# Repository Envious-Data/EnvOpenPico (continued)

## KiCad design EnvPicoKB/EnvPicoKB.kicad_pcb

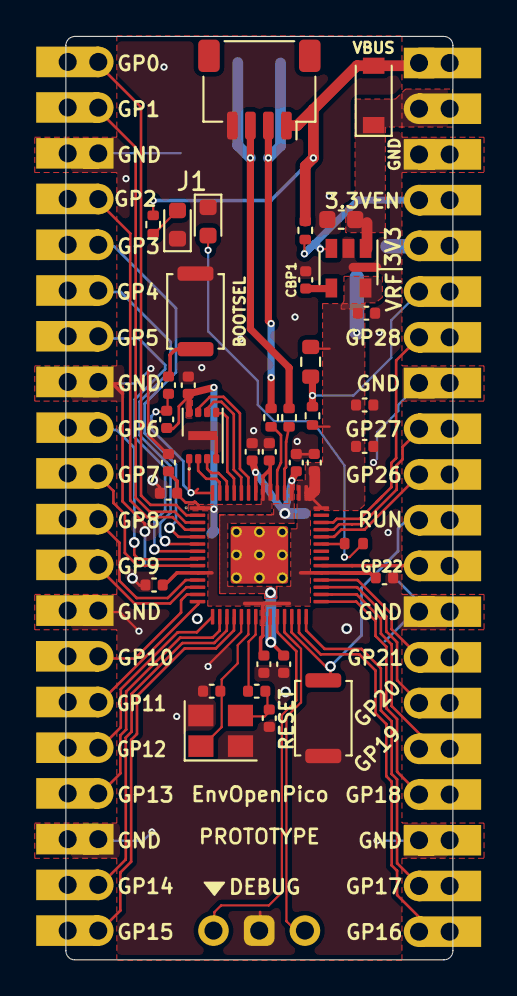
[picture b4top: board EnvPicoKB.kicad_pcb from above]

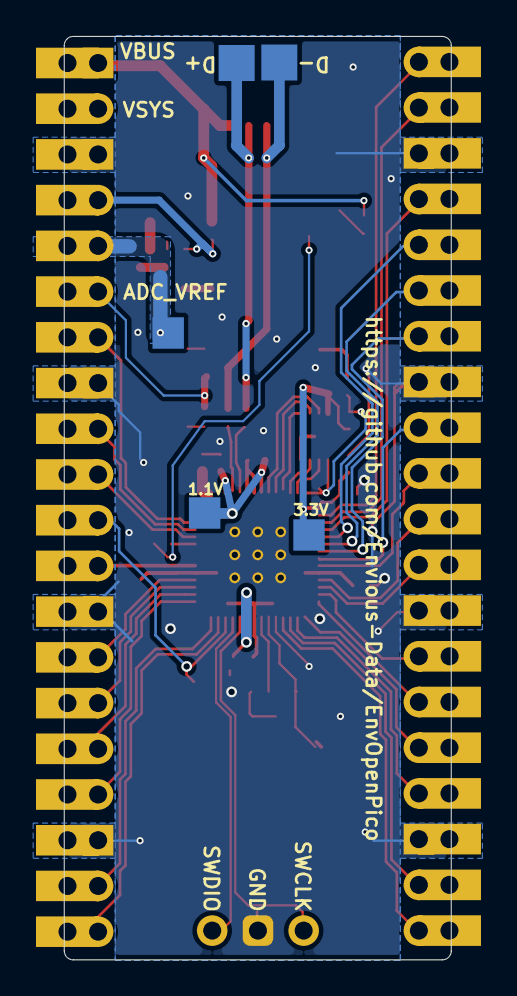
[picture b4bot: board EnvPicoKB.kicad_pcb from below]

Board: 2 copper layers, 21.5 x 51.3 mm, 46 parts (7 on the bottom side), 54 nets.

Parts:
C1: 10uf 0603 6.3V; C_0603_1608Metric
C2, C19: 22pf 0402; C_0402_1005Metric
C3, C10: 1uf 0402; C_0402_1005Metric
C4, C17: 10uf 0402; C_0402_1005Metric
C5, C6, C7, C8, C11, C13, C14, C15, C16, C18: 100nf 0402; C_0402_1005Metric
CBP1: 10uf 0402; C_0402_1005Metric
D1: 1N4002W; D_SOD-123
D3: LED_0603; LED_0603_1608Metric
FLASH1: W25Q16FWUXIE; SON-8-1EP_3x2mm_P0.5mm_EP1.4x1.6mm
J1: Conn_01x04; JST_SH_SM04B-SRSS-TB_1x04-1MP_P1.00mm_Horizontal
J2: SKRKAEE020; SW_Push_SPST_NO_Alps_SKRK
J3, J4: 2.54mm header 01x20; PinHeader_1x20_P2.54mm_Vertical
J5: Conn_01x03_Male; PinHeader_1x03_P2.54mm_Vertical
PWRLED1: LED_0603; LED_0603_1608Metric
R1, R11: 1K 0402 Resistor; C_0402_1005Metric
R2: 10K 0402; C_0402_1005Metric
R3, R4: 27 0402 Resistor; R_0402_1005Metric
R7: 100K 0402 resistor; R_0402_1005Metric
R8: 470 0402 Resistor; R_0402_1005Metric
R9: 200 0603; R_0603_1608Metric
R10: 1 0402; R_0402_1005Metric
R12: 5.1K 0402 Resistor; R_0402_1005Metric
RSW1: SKRKAEE020; SW_Push_SPST_NO_Alps_SKRK
TP1, TP2, TP6, TP7, TP8: TestPoint; TestPoint_Pad_D1.0mm
U1: TLV75533PDBVR; SOT-23-5
U3: RP2040; RP2040-QFN-56
Y1: 3225_4P; Crystal_SMD_3225-4Pin_3.2x2.5mm

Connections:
3V3_EN: J4.4, R7.1, U1.3
+1V1: C3.1, C6.1, C7.1, TP7.1, U3.23, U3.45, U3.50
+3V3: C4.1, C5.1, C8.1, C10.1, C11.1, C13.1, C14.1, C15.1, C16.1, C17.1, C18.1, FLASH1.8, J4.5, R2.1, R9.1, R10.2, TP6.1, TP8.1, U1.5, U3.1, U3.10, U3.22, U3.33, U3.42, U3.43, U3.44, U3.48, U3.49
/ADC_VREF: J4.6, R9.2, R10.1
/GPIO0: J3.20, U3.2
/GPIO1: J3.19, U3.3
/GPIO2: J3.17, U3.4
/GPIO3: J3.16, U3.5
/GPIO4: J3.15, U3.6
/GPIO5: J3.14, U3.7
/GPIO6: J3.12, U3.8
/GPIO7: J3.11, U3.9
/GPIO8: J3.10, U3.11
/GPIO9: J3.9, U3.12
/GPIO10: J3.7, U3.13
/GPIO11: J3.6, U3.14
/GPIO12: J3.5, U3.15
/GPIO13: J3.4, U3.16
/GPIO14: J3.2, U3.17
/GPIO15: J3.1, U3.18
/GPIO16: J4.20, U3.27
/GPIO17: J4.19, U3.28
/GPIO18: J4.17, U3.29
/GPIO19: J4.16, U3.30
/GPIO20: J4.15, U3.31
/GPIO21: J4.14, U3.32
/GPIO22: J4.12, U3.34
/GPIO25: R8.2, U3.37
/GPIO26_ADC0: J4.10, U3.38
/GPIO27_ADC1: J4.9, U3.39
/GPIO28_ADC2: J4.7, U3.40
/QSPI_SCLK: FLASH1.6, U3.52
/QSPI_SD0: FLASH1.5, U3.53
/QSPI_SD1: FLASH1.2, U3.55
/QSPI_SD2: FLASH1.3, U3.54
/QSPI_SD3: FLASH1.7, U3.51
/QSPI_SS: FLASH1.1, R1.1, R2.2, U3.56
/RUN: J4.11, RSW1.2, U3.26
/SWCLK: J5.1, U3.24
/SWD: J5.3, U3.25
/~USB_BOOT: J2.1, R1.2
GND: C1.2, C2.1, C3.2, C4.2, C5.2, C6.2, C7.2, C8.2, C10.2, C11.2, C13.2, C14.2, C15.2, C16.2, C17.2, C18.2, C19.1, CBP1.2, D3.1, FLASH1.4, FLASH1.9, J1.4, J2.2, J3.3, J3.8, J3.13, J3.18, J4.3, J4.8, J4.13, J4.18, J5.2, PWRLED1.1, RSW1.1, U1.2, U3.19, U3.57, Y1.2, Y1.4
unnamed: C19.2, R11.2, Y1.3
unnamed: CBP1.1, U1.4
unnamed: D3.2, R8.1
unnamed: PWRLED1.2, R12.1
unnamed: R3.2, U3.47
unnamed: R4.2, U3.46
USB_D+: J1.2, R3.1, TP1.1
USB_D-: J1.3, R4.1, TP2.1
VBUS: D1.2, J1.1, J4.1, R7.2, R12.2
VSYS: C1.1, D1.1, J4.2, U1.1
XIN: C2.2, U3.20, Y1.1
XOUT: R11.1, U3.21

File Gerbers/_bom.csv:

Comment,Designator,Footprint,LCSC
"10u","C1,C4,C17","Capacitor_SMD:C_0402_1005Metric",""
"1u","C3,C10","Capacitor_SMD:C_0402_1005Metric",""
"15p","C2","Capacitor_SMD:C_0402_1005Metric",""
"100n","C5,C6,C7,C8,C11,C13,C14,C15","Capacitor_SMD:C_0402_1005Metric",""
"0603 Diode 1N58","D2","Diode_SMD:D_0603_1608Metric",""
"LED 0402 YELLOW","D3","LED_SMD:LED_0402_1005Metric",""
"W25Q16JVUXIQ","FLASH1","Package_SON:SON-8-1EP_3x2mm_P0.5mm_EP1.4x1.6mm",""
"MountingHole","H1,H2,H3,H4","MountingHole:MountingHole_2.2mm_M2",""
"B3U-1000P","J2","Button_Switch_SMD:SW_SPST_B3U-1000P",""
"2.54mm header 01x20","J3,J4","Connector_PinHeader_2.54mm:PinHeader_1x20_P2.54mm_Vertical",""
"Conn_01x03_Male","J5","Connector_PinHeader_2.54mm:PinHeader_1x03_P2.54mm_Vertical",""
"1k","R1","Capacitor_SMD:C_0402_1005Metric",""
"DNF","R2","Capacitor_SMD:C_0402_1005Metric",""
" 27Ohms  0402 Resistor","R3","Capacitor_SMD:C_0402_1005Metric",""
" 27Ohms 0402 Resistor","R4","Capacitor_SMD:C_0402_1005Metric",""
"5.1K","R5,R6","Resistor_SMD:R_0402_1005Metric",""
"100K","R7","Resistor_SMD:R_0402_1005Metric",""
"470","R8","Resistor_SMD:R_0402_1005Metric",""
"SPX3819M5-L-3-3","U1","Package_TO_SOT_SMD:SOT-23-5",""
"RP2040","U3","RP2040_minimal:RP2040-QFN-56",""
"XO 32 12Mhz 3225 seiko","X1","Crystal:Crystal_SMD_SeikoEpson_TSX3225-4Pin_3.2x2.5mm",""
"TYPE-C-31-M-12","e1","HRO-TYPE-C31-M-12:HRO-TYPE-C-31-M-12",""

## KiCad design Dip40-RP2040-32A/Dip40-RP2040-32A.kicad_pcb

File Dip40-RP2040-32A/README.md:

# Dip40-RP2040-**32A**

This is another Dip40 RP2040 board but with a pinout a bit more like an Atmel ATmega32A.

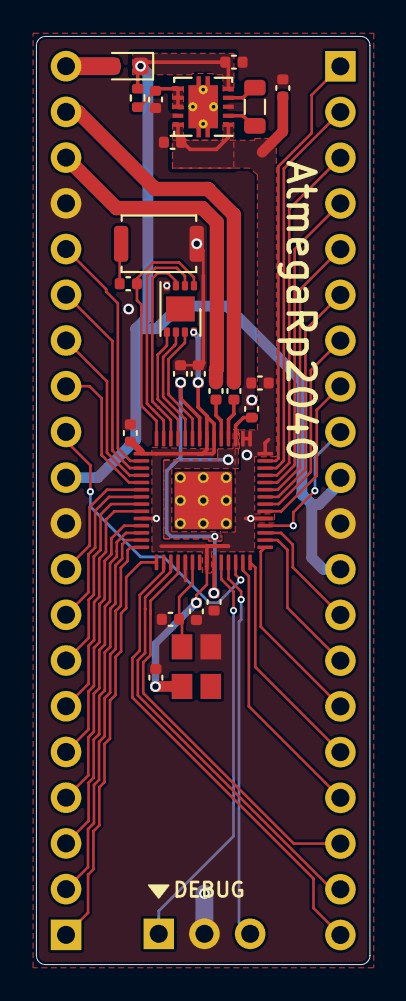
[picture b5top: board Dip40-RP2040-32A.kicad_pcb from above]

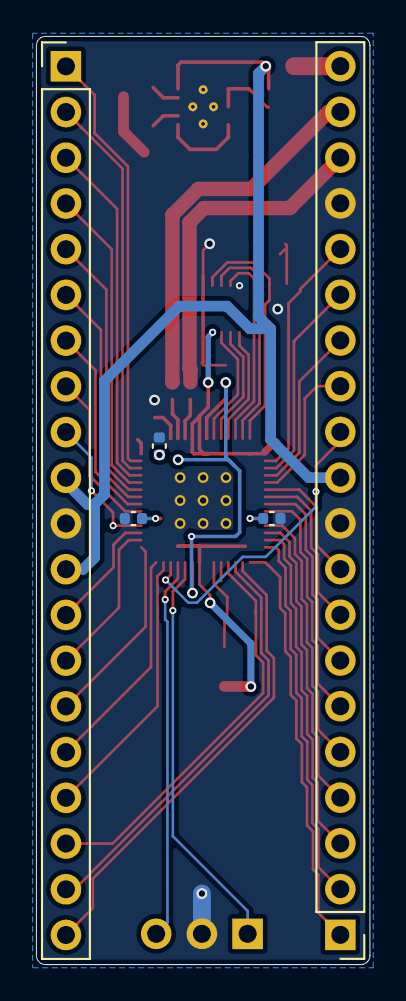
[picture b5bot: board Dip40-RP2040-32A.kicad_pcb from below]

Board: 2 copper layers, 18.5 x 51.6 mm, 30 parts (5 on the bottom side), 52 nets.

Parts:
C1, C4, C9, C17: 10uf 0402; C_0402_1005Metric
C2: 15pf 0402; C_0402_1005Metric
C3, C10: 1uf 0402; C_0402_1005Metric
C5, C6, C7, C8, C11, C13, C14, C15: 100nf 0402; C_0402_1005Metric
C12: 0.1uf 0402; C_0402_1005Metric
D1: SCHOTTKY DIODE; D_0603_1608Metric
FLASH1: W25Q16; SON-8-1EP_3x2mm_P0.5mm_EP1.4x1.6mm
J2: SKRKAEE020; SW_Push_SPST_NO_Alps_SKRK
J3, J4: 2.54mm header 01x20; PinHeader_1x20_P2.54mm_Vertical
J5: Conn_01x03_Male; PinHeader_1x03_P2.54mm_Vertical
L1: Inductor 2.2uh; L_0805_2012Metric
R1: 1k Resistor; C_0402_1005Metric
R3, R4: 27Ohms 0402 Resistor; C_0402_1005Metric
R7: 100ohm; R_0402_1005Metric
U1: TPS63002; Texas_DRC0010J_ThermalVias
U3: RP2040; RP2040-QFN-56
X1: XO 32 12Mhz 3225 seiko; Crystal_SMD_SeikoEpson_TSX3225-4Pin_3.2x2.5mm

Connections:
3V3_EN: C12.1, R7.2, U1.6, U1.7, U1.8
+1V1: C3.1, C6.1, C7.1, U3.23, U3.45, U3.50
+3V3: C4.1, C5.1, C8.1, C9.1, C10.1, C11.1, C13.1, C14.1, C15.1, C17.1, FLASH1.8, U1.1, U1.10, U3.1, U3.10, U3.22, U3.33, U3.42, U3.43, U3.44, U3.48, U3.49, X1.4
/GPIO0: J3.16, U3.2
/GPIO1: J3.15, U3.3
/GPIO2: J3.14, U3.4
/GPIO3: J3.13, U3.5
/GPIO4: J3.9, U3.6
/GPIO5: J3.8, U3.7
/GPIO6: J3.7, U3.8
/GPIO7: J3.6, U3.9
/GPIO8: J3.5, U3.11
/GPIO9: J3.4, U3.12
/GPIO10: J3.3, U3.13
/GPIO11: J3.2, U3.14
/GPIO12: J3.1, U3.15
/GPIO13: J4.20, U3.16
/GPIO14: J4.19, U3.17
/GPIO15: J4.18, U3.18
/GPIO16: J4.17, U3.27
/GPIO17: J4.16, U3.28
/GPIO18: J4.15, U3.29
/GPIO19: J4.14, U3.30
/GPIO20: J4.13, U3.31
/GPIO21: J4.9, U3.32
/GPIO22: J4.8, U3.34
/GPIO23: J4.7, U3.35
/GPIO24: J4.6, U3.36
/GPIO25: J4.5, U3.37
/GPIO26_ADC0: J4.4, U3.38
/GPIO27_ADC1: J4.3, U3.39
/GPIO28_ADC2: J4.2, U3.40
/GPIO29_ADC3: J4.1, U3.41
/QSPI_SCLK: FLASH1.6, U3.52
/QSPI_SD0: FLASH1.5, U3.53
/QSPI_SD1: FLASH1.2, U3.55
/QSPI_SD2: FLASH1.3, U3.54
/QSPI_SD3: FLASH1.7, U3.51
/QSPI_SS: FLASH1.1, R1.1, U3.56
/RUN: J3.12, U3.26
/SWCLK: J5.1, U3.24
/SWD: J5.3, U3.25
/USB_D+: J3.18, R3.1
/USB_D-: J3.19, R4.1
/XIN: C2.2, U3.20, X1.3
/~USB_BOOT: J2.1, R1.2
GND: C1.2, C2.1, C3.2, C4.2, C5.2, C6.2, C7.2, C8.2, C9.2, C10.2, C11.2, C12.2, C13.2, C14.2, C15.2, C17.2, FLASH1.4, J2.2, J3.10, J3.17, J4.11, J5.2, U1.3, U1.9, U1.11, U3.19, U3.57, X1.2
unnamed: L1.1, U1.4
unnamed: L1.2, U1.2
unnamed: R3.2, U3.47
unnamed: R4.2, U3.46
VBUS: C1.1, D1.1, D1.2, J3.11, J3.20, J4.10, J4.12, R7.1, U1.5

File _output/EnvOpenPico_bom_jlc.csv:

"Comment","Designator","Footprint","LCSC Part #"
"10uf 0402","C1,C4,C17,C9","C_0402_1005Metric","no_part_number"
"15pf 0402","C2","C_0402_1005Metric","no_part_number"
"100nf 0402","C6,C7,C5,C11,C15,C14,C13,C8","C_0402_1005Metric","no_part_number"
"1uf 0402","C10,C3","C_0402_1005Metric","no_part_number"
"0.1uf 0402","C12","C_0402_1005Metric","no_part_number"
"SCHOTTKY DIODE","D1","D_0603_1608Metric","no_part_number"
"LED 0402 YELLOW","D3","LED_0402_1005Metric","no_part_number"
"TYPE-C-31-M-12","e1","HRO-TYPE-C-31-M-12","no_part_number"
"W25Q16","FLASH1","SOIJ-8_5.3x5.3mm_P1.27mm","no_part_number"
"MountingHole","H1,H2,H3,H4","MountingHole_2.2mm_M2","no_part_number"
"B3U-1000P","J2","SW_SPST_B3U-1000P","no_part_number"
"2.54mm header 01x20","J4,J3","PinHeader_1x20_P2.54mm_Vertical","no_part_number"
"Conn_01x03_Male","J5","PinHeader_1x03_P2.54mm_Vertical","no_part_number"
"Inductor 2.2uh","L1","L_0805_2012Metric","no_part_number"
"1k Resistor","R1","C_0402_1005Metric","no_part_number"
"DNF","R2","C_0402_1005Metric","no_part_number"
" 27Ohms  0402 Resistor","R3","C_0402_1005Metric","no_part_number"
" 27Ohms 0402 Resistor","R4","C_0402_1005Metric","no_part_number"
"5.1K","R6,R5","R_0402_1005Metric","no_part_number"
"100ohm","R7","R_0402_1005Metric","no_part_number"
"470 ohm resistor","R8","R_0402_1005Metric","no_part_number"
"TPS63002","U1","Texas_DRC0010J_ThermalVias","no_part_number"
"RP2040","U3","RP2040-QFN-56","no_part_number"
"XO 32 12Mhz 3225 seiko","X1","Crystal_SMD_SeikoEpson_TSX3225-4Pin_3.2x2.5mm","no_part_number"

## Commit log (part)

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2021-04-26 Initial commit +1
2021-04-26 more progress bits
2021-04-26 did more things!
2021-04-26 progress+1
2021-04-26 progress +2
2021-04-26 Added a Image
2021-04-27 Redesign
    I need sleep.
2021-04-27 Swapped Crystal for smaller XO oscillator
    + some general other changes
2021-04-28 added more decoupling capacitors+++others
2021-04-28 Replaced MicroB with Type-C
2021-04-28 I forgot what I went to adjust but I did something or another.
2021-04-28 replaced the 3.3V out diode for a smaller one
2021-04-28 Made the board 0.09mm wider and adjusted the ground planes
2021-04-28 Moved some vias to account for mechanical damage
2021-04-29 Updated image
    sleep deprivation lol.
2021-04-29 Changed Regulator for one with an enable pin
2021-04-29 added some more info to README
2021-04-30 Changed SOIC Flash for WSON Flash
    also added a button instead of 1mm pitch headers along with general other track adjustments and stuff.
2021-05-01 Updated some components to be JLCPCB SMT Assembly compatible
2021-05-01 Added a Bunch of notes and useful info to the schematic
2021-05-01 Added some more notes
2021-05-01 Updated Readme and Picture
2021-05-03 Changed flash part number for a compatible version incase JLC has stock
2021-05-03 Some general changes and house keeping
2021-05-05 some silkscreen adjustments and a couple added notes to schematic
2021-05-14 Updated Gerber Files
2021-05-14 Corrected some notes
2021-05-15 some more adjustments to correct auto filling fields in JLCPCB
2021-05-20 Replaced Flash footprint with USON-8/3x2mm to match received samples
2021-05-20 Generated Gerber files.
2021-06-04 Added Castellations to sides of PCB
2021-06-07 Generated updated Gerber files with castelations
2021-06-07 unsure if permanent but can get a hold of components RPI Pico uses
2021-06-08 Added some vias and tweaked some placements and adjustments
2021-06-12 Changed out some parts and added more details to their BOM comments
2021-06-26 Swapped RT6150GQW for TPS63002
2021-06-28 Swapped flash chip for larger version, JLCPCB now stocks the RP2040
2021-06-28 Generated updated gerber
2021-06-30 Changed button, generated JLCPCB compatible gerbers
2021-07-23 Corrected some library bits.
2021-07-23 Organized repo + updated README.md
2021-07-23 Created Dip40 sized version
2021-07-23 Create pinout concept for 32a version
2021-07-24 created and worked on 32a-like pinout version.
2021-07-26 small corrections and added a couple test points.
2021-07-26 Rotated Oscillator by 180 degrees
2021-07-26 corrected reveresed usb debug pads, added gnd debug pad and incremented revision number.
2021-07-27 Adjusted the placement of some components and added some filled zones.
2021-07-27 moved some components to better locations and also created more filled areas
2021-07-29 Hopefully implemented ADC_VREF Correctly on dip40 and pico verrsion
2021-07-29 updated readme and corrected a capacitor placement.
2021-07-31 corrected capacitor placement.
2021-07-31 moved some more components to better places.
2021-07-31 added some extra notes and moved some parts about, added some test points.
2021-08-05 moved C11 on 32A board closer to the MCU
2021-08-13 started work on a RP2040 board with a ESP BT/WIFI slave and a battery charge/management IC
2021-08-13 generated some updated gerbers
2021-08-14 some useful updates
2021-08-14 added some silkscreen pin lables where possible on the front (they'll be on the back otherwise.)
2021-08-14 changed notes regarding D1 and what type should be installed.
2021-08-14 Corrected all the via placements so they dont cause issues and removed some redundant parts
2021-08-14 corrected via sizes and placements.
2021-08-15 replaced XO with crystal due to stock issues, and some general cleanups and corrections
2021-08-18 added keepout zones around the pins to avoid shorts
2021-08-18 woops made sure keepout zone was on both sides of the pcb.
2021-08-18 some housekeeping, i.e cleaning up comments and various other bits.
2021-08-18 Generated up to date Gerbers.
2021-08-23 removed ESP32 and wifi bits for now, will re-add something later on with further testing.
2021-08-23 cleanup + sorted out some spacing and trace misalignment.
2021-08-23 moved the battery connector to the bottom of the board and rotated the debug header 90 degrees to fit along side.
2021-08-24 Added Reset button + general other tweaks, cleanups and changes.
2021-08-25 Swapped TPS6300x for TLV75533PDBVR due to stock issues.
2021-08-25 changed some labels to make part selection easier
2021-08-26 added a optinal bypass resistor cBP1 incase an alternative SOT-23-5 regulator is installed. + moved more pinout silkscreen to the front.
2021-08-26 small adjustment to a few tracks and vias to allow for more ground plane coverage.
2021-09-04 generated upto date Gerber (also made sure csv files are uploaded to github)
2021-09-04 made some silkscreen more readable and moved TP pads for USB closer to where they are on the RPI Pico.
2021-09-09 Added a small note on a stocked Flash IC that JLC has loads of (as of right now.)
2021-09-11 Updated Gerber files for Rev 1.0
2021-09-11 added a resistor that I missed and once again generated updated gerbers lol.
2021-09-13 some experimentation with panelization
2021-09-14 Generated updated gerbers, replaced type-c HS with ASM.
2021-09-14 corrected footprints for R3 and R4 in the schematic
2021-09-14 Added then removed agnd, fixed pin header row silkscreen and removed R3/R4 silkscreen ref
2021-09-14 dont mind my indecision, generated updated gerbers and stuff.
2021-09-14 Generated Fixed Gerber.
    There was an odd issue where if the reference wasn't ALL CAPS it didn't show up in the parts list.
2021-09-14 Added a 5V power LED
2021-09-14 swapped LEDs for 0603 size due to better avaliability.
2021-10-02 some general checks and generated a gerber
2021-10-16 added mousebite markers
2021-10-16 updated panel script
2021-10-16 added some markers for panelization
2021-10-16 gave up with panel due to MOQs for now
2021-10-20 moved some vias off some pads.
2021-10-28 corrected some things, it appears GD25Q40 doesnt work with the RP2040 but the GD25Q16/32/64 work fine.
2021-10-28 some small adjustments
2021-10-28 added some notes and also various tweaks n what not.
2021-10-28 updated revision to 1.1
2021-10-28 changed JST connector for more common type, adjusted some parts to do with flash
2021-10-29 updated readmes
2021-10-29 enlarged USB TP Pads and aligned USB port to center.
2021-10-30 edited small note in schematic for CBP1
2021-11-01 Generated updated Gerber for PCBWAY
2021-11-02 committed updated Gerber files for PCBWAY
2021-11-06 corrected library symbol for reset button
2021-11-11 Generated updated Gerber as requested.
2021-11-21 Generated updated gerber and fixed 2 random issues as per DRC
2021-11-25 Created Keyboard specific version that has a JST connector compatible with the unified daughterboard by ai03-2727
2021-11-26 woops, wrong JST connector lol.
2021-12-05 updated gerbers and added generated gerber for version with BCPW Loco
2021-12-09 Created Elite-C like board but with RP2040
2021-12-09 moved some parts about to fit optional bypass resistor
2021-12-09 shortened pcb, added bypass resistor, pads for SPI flash and supporting decoupling capacitor
2021-12-17 swapped various parts to 0201 and added fuse between VSYS and linear reg
2021-12-25 corrected a placeholder reference I forgot to label as such, also added more comments in the schematic for the main design.
2021-12-27 removed Dip40 versions, changed fuse on main version to 805 size and added part number.
2022-01-11 Lots of changes, redid elite-c version, added more debug pads to main version and various tweaks among other things.
2022-01-11 Swapped regulator for a smaller one, need to re-arrange some bits it seems.
2022-01-15 Added extra SPI Flash, swapped regulator due to stock issues, updated git ignore.
2022-01-16 some tiny tweaks to placement and traces
2022-01-24 Added 0402 ferrite for noise suppression and added a seperate ground plane under the Analogue pins.
    Analogue stuff is basically voodoo it seems.
2022-03-01 tiny cleanup, generated updated gerbers
2022-03-07 swapped out a 10K 0201 for a 10K 0402
2022-03-07 forgot to remove some silkscreen references
2022-03-25 updated a couple readmes.
2022-03-29 PCBWAY Sponsor / Added pictures
2022-03-29 Moved pictures folder
2022-03-29 fix small typo
2022-04-27 removed logo for now
2022-04-27 swapped some parts back to 0402 size due to stock issues among fixes.
2022-05-10 generated updated gerbers
2022-05-18 added eeprom ic on GP29 and GP28
2022-05-21 some silkscreen fixes and generated updated gerber/cpl/bom
2022-05-23 removed some parts and swapped flash to soic package for stock reasons.
2022-06-04 made some changes in the schematic to conform more with the USB Spec,
2022-06-11 Generated WRL model for Blender
2022-06-15 implemented schematic changes and replaced flash with smaller one
2022-06-16 removed KB version since its now irrelevant, Generated updated gerbers, bom and CPL as well as made chnges to the PCB based on prior schematic adjustments
2022-06-24 dont remember what I changed but commit for safety
2022-06-27 faff and things, no important changes.
2022-06-30 small tweaks + generated gerbers
2022-06-30 matched pinout of pro-micro a bit more among various other changes.
2022-06-30 modified board to fit with bastardKB's standard, added vbus sense, changed pinout, removed reset button and moved bootsel, removed SPI EEPROM as its not supported.
2022-07-01 lots of changes, swapped many parts to 0402, swapped SOT regulator to small WSON, made sure there is proper parity between footprint and value, etc etc etc
2022-07-06 made some smaller components generated new gerber
2022-07-07 swapped flash for one that was in stock.
2022-07-21 various updates including README
2022-07-24 tiny change.
2022-07-29 preparation for order.
2022-08-05 incr version, added mosfet and led for GP23, marked GP24, tiny bits of cleanup and DRC checks.
2022-10-06 added diode after VBUS to make sure VBUS Detect can work properly.
2022-10-14 made various improvements to design such as swapping vbus for vsys on the raw pin
2022-10-30 General re-work of board to ensure less chance of failure
2022-10-31 small change to one value to autofill
2022-11-29 small various tweaks and fixes
2022-11-29 updated image
2022-11-29 tiny fix on one of the trace widths
2022-11-29 removed pointless silkscreens
2022-12-08 some small fixes regarding the silkscreen and 3d models
2022-12-08 bumped minimum clearance and trace thickness to 0.15mm and re-did all traces with less clearance or less thickness
2022-12-23 swapped regulator to sot-23-3 version
2022-12-23 swapped crystal for 3225 version
2022-12-24 missing files commit
2023-01-09 generated gerbers with latest changes
2023-01-09 moved csvs to gerber folder
2023-02-13 replaced flash symbol with built in one, some clearance fixes
2023-02-14 overhauled battery version, not many changes other than increasing clearance across the board
2023-02-14 added missing bootsel silkscreen
2023-02-14 generated updated gerbers for EliteMicro2040
2023-02-20 few small tweaks here and there
2023-03-04 fixed major potential oversight on 3V3_EN being tied to VBUS rather than VSYS.
2023-03-04 fixed ADC_AVDD being tied to 3V3 incorrectly, various tweaks and adjustments to part positions to ensure everything fits properly
2023-03-04 added some unimportant symbols
2023-03-06 re-aligned some parts to be properly centered, not important but wanted to do it.
2023-06-11 small fix to a couple traces
2023-06-11 Created Experimental version to fit all 0402 components and a top mount type-c port
2023-06-11 disregard creation of experimental version
2023-06-11 corrected some bits
2023-06-11 fixed up some things in the gerber, cpl and bom
2023-10-10 swapped the symbol and footprint for the type-c port to the kicad built in one
2024-03-27 corrected picture of lipo version (it doesnt have a wifi slave anymore)
2024-03-27 updated outdated readme.
2024-08-09 started work on making RP235XX boards
2024-11-03 made many corrections to RP2040 pico board, silkscreen, positioning, footprint, any errors I could find.
